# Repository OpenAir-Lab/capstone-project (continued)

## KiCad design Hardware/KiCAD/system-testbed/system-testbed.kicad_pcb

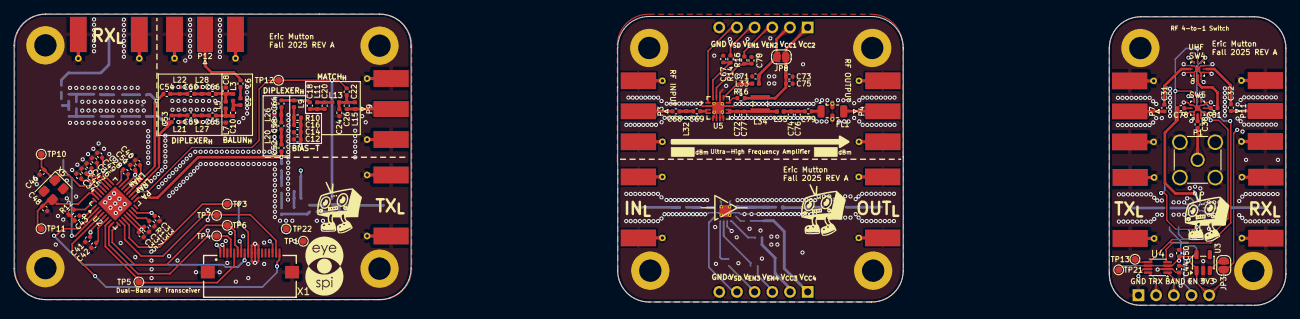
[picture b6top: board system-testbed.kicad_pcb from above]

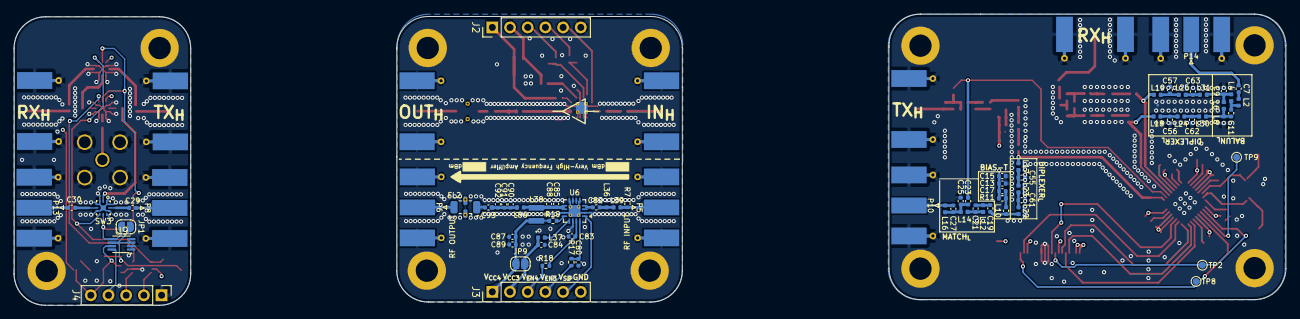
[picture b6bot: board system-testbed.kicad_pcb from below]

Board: 4 copper layers, 182.6 x 41.8 mm, 196 parts (76 on the bottom side), 110 nets.

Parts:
C6, C8, C10: 5.1pF; C_0402_1005Metric
C7, C9, C11, C21, C23: 12pF; C_0402_1005Metric
C12: 100p; C_0402_1005Metric
C13, C17, C38, C79, C88: 100pF; C_0402_1005Metric
C14, C40: 10n; C_0402_1005Metric
C15: 10nF; C_0402_1005Metric
C16: 56p; C_0402_1005Metric
C18: 39p; C_0402_1005Metric
C19: 82pF; C_0402_1005Metric
C20: 2.2p; C_0402_1005Metric
C22, C29, C30, C31, C32, C67, C70, C75, C78, C80, C81, C83, C89: 1nF; C_0402_1005Metric
C24: 6.2p; C_0402_1005Metric
C25: 15pF; C_0402_1005Metric
C26, C27: 1.2p; C_0402_1005Metric
C28: 1.5n; C_0402_1005Metric
C33, C34, C35, C36, C37, C41, C43, C45, C47, C49, C51: 47n; C_0402_1005Metric
C42: 220n; C_0402_1005Metric
C44, C50, C84: 1uF; C_0402_1005Metric
C46, C48: 15p; C_0402_1005Metric
C52, C53, C54, C64, C65, C66: 4.7pF; C_0402_1005Metric
C55, C56, C57, C61, C62, C63, C92: 18pF; C_0402_1005Metric
C58, C59, C60: 2.7pF; C_0402_1005Metric
C68: 10pF; C_0402_1005Metric
C69, C72: 33pF; C_0402_1005Metric
C71: 0.1uF; C_0402_1005Metric
C73, C87: 10uF; C_0402_1005Metric
C74: 27pF; C_0402_1005Metric
C76: 3pF; C_0402_1005Metric
C77: 6.8pF; C_0402_1005Metric
C82, C93: 220pF; C_0402_1005Metric
C85: 270pF; C_0402_1005Metric
C90, C91: 47pF; C_0402_1005Metric
FL1: LFCN-490; Filter_Mini-Circuits_FV1206
FL2: LFCN-160; Filter_Mini-Circuits_FV1206
H1, H1#2, H2, H3, H3#2, H4, H5, H5#2, H6, H8: M3; MountingHole_3.2mm_M3_ISO14580_Pad
J2, J3: Conn_01x06_Pin; PinHeader_1x06_P2.54mm_Vertical
J4: RF Switch; PinHeader_1x05_P2.54mm_Vertical
JP1, JP3: EN; SolderJumper-2_P1.3mm_Open_RoundedPad1.0x1.5mm
JP8, JP9: Single V_{CC}; SolderJumper-2_P1.3mm_Open_RoundedPad1.0x1.5mm
L1, L20, L21, L22, L26, L27, L28: 15nH; L_0402_1005Metric
L2: 39nH; L_0402_1005Metric
L3, L7: 27nH; L_0402_1005Metric
L4, L8: 82nH; L_0402_1005Metric
L5, L9: 56n; L_0402_1005Metric
L6: 150n; L_0402_1005Metric
L10: 220nH; C_0402_1005Metric
L11: 15n; L_0402_1005Metric
L12: 18nH; L_0402_1005Metric
L13: 43n; L_0402_1005Metric
L14, L23, L24, L25: 100nH; L_0402_1005Metric
L15: 22n; L_0402_1005Metric
L16, L17, L18, L19, L29, L30, L31, L39: 68nH; L_0402_1005Metric
L32: 10nH; L_0402_1005Metric
L33: 20nH; L_0402_1005Metric
L34: 23nH; 0908SQ23NGLC
L35: 2.4nH; L_0402_1005Metric
L36: 150nH; L_0402_1005Metric
L37: 56nH; L_0402_1005Metric
L38: 1uH; IND_IMSC1008AZER_VIS
L86: 9.1nH; L_0402_1005Metric
P1: SMA; SMA_Amphenol_901-144_Vertical
P3, P4, P5, P6, P7, P8, P9, P10, P11, P12, P13, P14: SMA; SMA_Molex_73251-1153_EdgeMount_Horizontal
R7: 350; R_0402_1005Metric
R10: 18; R_0402_1005Metric
R11: 22; R_0402_1005Metric
R12: 0R; R_0402_1005Metric
R13: 56k; R_0402_1005Metric
R14, R17: 1.27k; R_0402_1005Metric
R15, R18: 3.0k; R_0402_1005Metric
R16, R19: 0k; R_0402_1005Metric
SW3, SW4, SW5: SKY13330-397LF
TP1: +3.3V; TestPoint_Pad_D1.0mm
TP2: NRST; TestPoint_Pad_D1.0mm
TP3: NCS; TestPoint_Pad_D1.0mm
TP4: SCLK; TestPoint_Pad_D1.0mm
TP5: MOSI; TestPoint_Pad_D1.0mm
TP6: IO1/MISO; TestPoint_Pad_D1.0mm
TP7: IO0; TestPoint_Pad_D1.0mm
TP8: IO2; TestPoint_Pad_D1.0mm
TP9: IO3; TestPoint_Pad_D1.0mm
TP10: X1; TestPoint_Pad_D1.0mm
TP11: X2; TestPoint_Pad_D1.0mm
TP12: TRX_SW; TestPoint_Pad_D1.0mm
TP13: TRX_SW_{+2.5V}; TestPoint_Pad_D1.0mm
TP21: +2.5V; TestPoint_Pad_D1.0mm
TP22: GND; TestPoint_Pad_D1.0mm
U2: CC1200RHBR; QFN-32-1EP_5x5mm_P0.5mm_EP3.45x3.45mm
U3: LP5907MFX-2.5; SOT-23-5
U4, U9: TXS0101DBV; VSSOP-8_2.3x2mm_P0.5mm
U5, U6: GRF5604; QFN-16-1EP_3x3mm_P0.5mm_EP1.7x1.7mm_ThermalVias
U$22: EYESPI_MINI_LOGO
X1: EYESPI; Adafruit EYESPI FPC Connector
X5: 40 MHz; Crystal_SMD_3225-4Pin_3.2x2.5mm

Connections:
+2.5V: C50.2, JP1.1 (A), TP21.1, U3.5 (OUT), U4.3 (VCCA), U4.6 (OE), U9.3 (VCCA), U9.6 (OE)
+3.3V: C12.1, C13.1, C14.1, C15.1, C16.1, C17.1, C33.1, C35.1, C37.1, C41.1, C43.1, C44.2, C45.1, C47.1, C49.1, C51.1, C71.1, C84.1, J2.2, J3.2, J4.5, JP3.1 (A), JP8.1 (A), JP9.1 (A), L33.1, L37.1, R10.1, R11.1, SW3.9 (VDD), SW4.9 (VDD), SW5.9 (VDD), TP1.1, U2.1 (VDD_GUARD), U2.5 (DVDD), U2.12 (DVDD), U2.13 (AVDD_IF), U2.15 (AVDD_RF), U2.22 (AVDD_SYNTH1), U2.25 (AVDD_PFD_CHP), U2.27 (AVDD_SYNTH2), U2.28 (AVDD_XOSC), U3.1 (IN), U4.7 (VCCB), U9.7 (VCCB), X1.1, X1.2, X1.7, X1.16
/RF Subsystem/EN_{BAND}: JP1.2 (B), SW3.8 (EN), SW4.8 (EN), SW5.8 (EN), U9.5 (A1)
/RF Subsystem/LNA_N: C54.1, L19.1, U2.20 (LNA_N)
/RF Subsystem/LNA_N_{UHF}: C8.1, C66.2, L3.1, L5.2
/RF Subsystem/LNA_N_{VHF}: C9.1, L4.1, L6.2, L31.2
/RF Subsystem/LNA_P: C53.1, L18.1, U2.19 (LNA_P)
/RF Subsystem/LNA_P_{UHF}: C10.1, C65.2, L5.1, L7.1
/RF Subsystem/LNA_P_{VHF}: C11.1, L6.1, L8.1, L30.1
/RF Subsystem/PA_{SHUTDOWN}: TP9.1, U2.3 (GPIO3)
/RF Subsystem/PA_{UHF}: C18.2, C64.2, L9.2
/RF Subsystem/PA_{VHF}: C19.2, L10.2, L29.2
/RF Subsystem/RF Frontend/RX_{UHF}: C32.1, P11.1 (In)
/RF Subsystem/RF Frontend/RX_{VHF}: C30.1, P13.1 (In)
/RF Subsystem/RF Frontend/TX_{UHF}: C31.1, P7.1 (In)
/RF Subsystem/RF Frontend/TX_{VHF}: C29.1, P8.1 (In)
/RF Subsystem/RF Frontend/UHF 6W PA/RF_{IN}: C68.1, P3.1 (In)
/RF Subsystem/RF Frontend/UHF 6W PA/RF_{OUT}: C79.2, FL1.1 (IN)
/RF Subsystem/RF Frontend/UHF 6W PA/V_{CC2}: C73.1, C75.1, J2.1, JP8.2 (B), L34.1, R16.2
/RF Subsystem/RF Frontend/UHF 6W PA/V_{EN1}: C67.1, R14.1, U5.16 (V_{ENABLE1})
/RF Subsystem/RF Frontend/UHF 6W PA/V_{EN2}: C70.1, R15.1, U5.15 (V_{ENABLE2})
/RF Subsystem/RF Frontend/UHF 6W PA/V_{ENABLE1}: J2.4, R14.2
/RF Subsystem/RF Frontend/UHF 6W PA/V_{ENABLE2}: J2.3, R15.2
/RF Subsystem/RF Frontend/UHF 6W PA/V_{SHUTDOWN}: J2.5, U5.1 (V_{SHUTDOWN})
/RF Subsystem/RF Frontend/VHF 6W PA/RF_{IN}: L39.1, P5.1 (In), R7.2
/RF Subsystem/RF Frontend/VHF 6W PA/RF_{OUT}: C93.2, FL2.1 (IN)
/RF Subsystem/RF Frontend/VHF 6W PA/V_{CC2}: C87.1, C89.1, J3.1, JP9.2 (B), L38.1, R19.2
/RF Subsystem/RF Frontend/VHF 6W PA/V_{EN1}: C80.1, R17.1, U6.16 (V_{ENABLE1})
/RF Subsystem/RF Frontend/VHF 6W PA/V_{EN2}: C83.1, R18.1, U6.15 (V_{ENABLE2})
/RF Subsystem/RF Frontend/VHF 6W PA/V_{ENABLE1}: J3.4, R17.2
/RF Subsystem/RF Frontend/VHF 6W PA/V_{ENABLE2}: J3.3, R18.2
/RF Subsystem/RF Frontend/VHF 6W PA/V_{SHUTDOWN}: J3.5, U6.1 (V_{SHUTDOWN})
/RF Subsystem/RFSW_{BAND}: J4.3, U4.1 (B2)
/RF Subsystem/RFSW_{EN}: J4.4, U9.8 (B1)
/RF Subsystem/RFSW_{TRX}: J4.2, U4.8 (B1)
/RF Subsystem/SW_BAND: SW5.7 (CTRL), U4.4 (A2)
/RF Subsystem/SW_TRX: SW3.7 (CTRL), SW4.7 (CTRL), TP13.1, U4.5 (A1)
/RF Subsystem/TRX_GPIO0: TP7.1, U2.10 (GPIO0), X1.17
/RF Subsystem/TRX_GPIO2: TP8.1, U2.4 (GPIO2), X1.18
/RF Subsystem/TRX_MISO: TP6.1, U2.9 (SO(GPIO1)), X1.6
/RF Subsystem/TRX_MOSI: TP5.1, U2.7 (SI), X1.5
/RF Subsystem/TRX_NCS: TP3.1, U2.11 (~CS), X1.9
/RF Subsystem/TRX_NRST: TP2.1, U2.2 (~RESET), X1.8
/RF Subsystem/TRX_PA: C52.1, L17.1, U2.17 (PA)
/RF Subsystem/TRX_SCLK: TP4.1, U2.8 (SCLK), X1.4
/RF Subsystem/TRX_X1: C46.2, TP10.1, U2.30 (XOSC_Q1), X5.1
/RF Subsystem/TRX_X2: C48.1, TP11.1, U2.31 (XOSC_Q2), X5.3
/RF Subsystem/TRX_{SW}: C22.1, C23.1, TP12.1, U2.18 (TRX_SW)
GND: C8.2, C9.2, C12.2, C13.2, C14.2, C15.2, C24.2, C25.2, C33.2, C34.2, C35.2, C36.2, C37.2, C40.2, C41.2, C42.2, C43.2, C44.1, C45.2, C46.1, C47.2, C48.2, C49.2, C50.1, C51.2, C55.2, C56.2, C57.2, C61.2, C62.2, C63.2, C67.2, C70.2, C71.2, C72.2, C73.2, C74.2, C75.2, C76.2, C77.2, C80.2, C83.2, C84.2, C85.2, C87.2, C88.2, C89.2, C90.2, C91.2, C92.2, FL1.2 (GND), FL1.4 (GND), FL2.2 (GND), FL2.4 (GND), H1.1, H1#2.1, H2.1, H3.1, H3#2.1, H4.1, H5.1, H5#2.1, H6.1, H8.1, J2.6, J3.6, J4.1, L7.2, L8.2, L20.2, L21.2, L22.2, L26.2, L27.2, L28.2, L32.2, L36.2, P1.2 (Ext), P3.2 (Ext), P4.2 (Ext), P5.2 (Ext), P6.2 (Ext), P7.2 (Ext), P8.2 (Ext), P9.2 (Ext), P10.2 (Ext), P11.2 (Ext), P12.2 (Ext), P13.2 (Ext), P14.2 (Ext), R7.1, R12.1, R13.2, SW3.1 (GND), SW3.3 (GND), SW3.4 (GND), SW3.6 (GND), SW3.10 (GND), SW3.12 (GND), SW3.13 (GND), SW4.1 (GND), SW4.3 (GND), SW4.4 (GND), SW4.6 (GND), SW4.10 (GND), SW4.12 (GND), SW4.13 (GND), SW5.1 (GND), SW5.3 (GND), SW5.4 (GND), SW5.6 (GND), SW5.10 (GND), SW5.12 (GND), SW5.13 (GND), TP22.1, U2.33 (GND_EP), U3.2 (GND), U4.2 (GND), U5.2 (GND/NC), U5.5 (GND/NC), U5.6 (GND/NC), U5.7 (GND/NC), U5.8 (GND/NC), U5.11 (GND/NC), U5.14 (GND/NC), U5.17 (PAD), U6.2 (GND/NC), U6.5 (GND/NC), U6.6 (GND/NC), U6.7 (GND/NC), U6.8 (GND/NC), U6.11 (GND/NC), U6.14 (GND/NC), U6.17 (PAD), U9.2 (GND), X1.3, X1.10, X1.11, X1.12, X1.Z1, X1.Z2, X5.2, X5.4
unnamed: C6.2, L1.1
unnamed: C7.2, L2.1
unnamed: C10.2, L1.2, L3.2
unnamed: C11.2, L2.2, L4.2
unnamed: C16.2, L9.1, R10.2
unnamed: C17.2, L10.1, R11.2
unnamed: C18.1, C20.2, L11.1
unnamed: C19.1, C21.2, L12.1
unnamed: C20.1, L11.2, L13.1
unnamed: C21.1, L12.2, L14.1
unnamed: C22.2, C24.1, C26.1, L13.2, L15.1
unnamed: C23.2, C25.1, C27.1, L14.2, L16.1
unnamed: C52.2, C58.1, L20.1
unnamed: C53.2, C59.1, L21.1
unnamed: C54.2, C60.1, L22.1
unnamed: C55.1, L17.2, L23.1
unnamed: C56.1, L18.2, L24.1
unnamed: C57.1, L19.2, L25.1
unnamed: C58.2, C64.1, L26.1
unnamed: C59.2, C65.1, L27.1
unnamed: C60.2, C66.1, L28.1
unnamed: C61.1, L23.2, L29.1
unnamed: C62.1, L24.2, L30.2
unnamed: C63.1, L25.2, L31.1
unnamed: C68.2, C69.1, L32.1
unnamed: C69.2, U5.3 (RF_{IN}), U5.4 (RF_{IN})
unnamed: C72.1, C77.1, L34.2, L35.1, U5.9 (RF_{OUT}), U5.10 (RF_{OUT})
unnamed: C74.1, C76.1, C79.1, L35.2
unnamed: C82.1, L36.1, L39.2
unnamed: C82.2, U6.3 (RF_{IN}), U6.4 (RF_{IN})
unnamed: C85.1, C88.1, L38.2, L86.1, U6.9 (RF_{OUT}), U6.10 (RF_{OUT})
unnamed: C90.1, C91.1, C92.1, C93.1, L86.2
unnamed: FL1.3 (OUT), P4.1 (In)
unnamed: FL2.3 (OUT), P6.1 (In)
unnamed: JP3.2 (B), U3.3 (EN)
unnamed: C38.1, P1.1 (In)
unnamed: C26.2, L15.2, P9.1 (In)
unnamed: C27.2, L16.2, P10.1 (In)
unnamed: C6.1, P12.1 (In)
unnamed: C7.1, P14.1 (In)
unnamed: C78.1, SW3.2 (RF1_COM)
unnamed: C29.2, SW3.11 (RF2)
unnamed: C30.2, SW3.5 (RF3)
unnamed: C81.1, SW4.2 (RF1_COM)
unnamed: C31.2, SW4.11 (RF2)
unnamed: C32.2, SW4.5 (RF3)
unnamed: C38.2, SW5.2 (RF1_COM)
unnamed: C78.2, SW5.11 (RF2)
unnamed: C81.2, SW5.5 (RF3)
unnamed: C42.1, U2.6 (DCPL)
unnamed: C36.1, U2.26 (DCPL_PFD_CHP)
unnamed: C40.1, U2.21 (DCPL_VCO)
unnamed: C34.1, U2.29 (DCPL_XOSC)
unnamed: R12.2, U2.32 (EXT_XOSC)
unnamed: C28.2, U2.23 (LPF0)
unnamed: C28.1, U2.24 (LPF1)
unnamed: R13.1, U2.14 (RBIAS)
unnamed: R16.1, U5.12 (V_{BIAS})
unnamed: L33.2, U5.13 (V_{CC1})
unnamed: R19.1, U6.12 (V_{BIAS})
unnamed: L37.2, U6.13 (V_{CC1})

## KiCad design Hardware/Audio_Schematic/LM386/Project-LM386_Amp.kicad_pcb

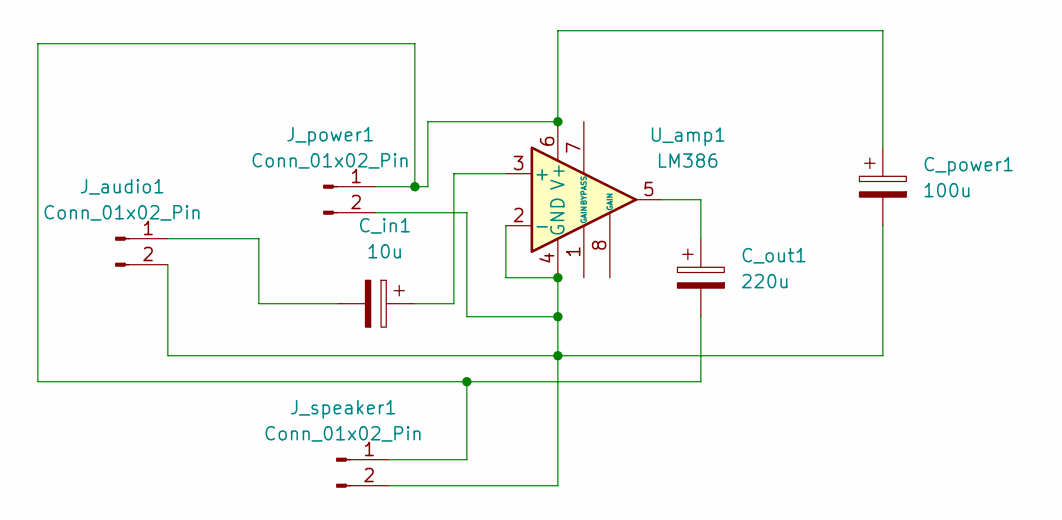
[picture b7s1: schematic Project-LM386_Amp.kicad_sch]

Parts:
C_in1: 10u; CP_Elec_6.3x5.3
C_out1: 220u; CP_Elec_6.3x5.3
C_power1: 100u; CP_Elec_6.3x5.3
J_audio1: Conn_01x02_Pin; PinHeader_1x02_P2.54mm_Vertical
J_power1: Conn_01x02_Pin; PinHeader_1x02_P2.54mm_Vertical
J_speaker1: Conn_01x02_Pin; PinHeader_1x02_P2.54mm_Vertical
U_amp1: LM386; HSOP-8-1EP_3.9x4.9mm_P1.27mm_EP2.3x2.3mm

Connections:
unnamed: C_out1.1, U_amp1.5
unnamed: C_in1.2, J_audio1.1
unnamed: C_power1.2, J_audio1.2, J_power1.2, J_speaker1.2, U_amp1.2 (-), U_amp1.4 (GND)
unnamed: C_out1.2, C_power1.1, J_power1.1, J_speaker1.1, U_amp1.6 (V+)
unnamed: C_in1.1, U_amp1.3 (+)

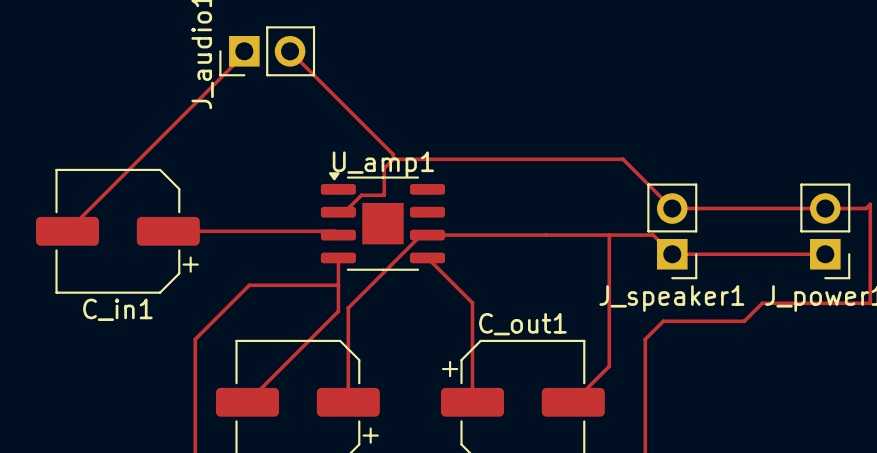
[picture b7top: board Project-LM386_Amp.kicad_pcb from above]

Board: 2 copper layers, 7 parts (0 on the bottom side), 5 nets.

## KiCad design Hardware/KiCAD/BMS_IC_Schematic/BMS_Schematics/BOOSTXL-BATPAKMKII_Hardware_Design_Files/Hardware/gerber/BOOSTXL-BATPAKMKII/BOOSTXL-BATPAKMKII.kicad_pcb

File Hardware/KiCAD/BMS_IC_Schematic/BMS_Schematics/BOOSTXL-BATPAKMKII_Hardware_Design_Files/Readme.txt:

BOOSTXL-BATPAKMKII Hardware Design Files v1.00.00
Texas Instruments, Inc.

********************************************************************************
Welcome to the BOOSTXL-BATPAKMKII BoosterPack!
********************************************************************************

In this package, you will find hardware design files that can help you quickly
get started on developing your own project.

Available in the 'Hardware' folder are the complete board schematic and layout,
bill of material, and Gerber files.

You can also find various web links in the 'Documentation' folder pointing to
the Tool Page, Quick Start Guide, and User's Guide.

For more resources, be sure to visit www.ti.com/tool/boostxl-batpakmkii

********************************************************************************
Revision History
********************************************************************************
Ver 1.00.00 - June 3rd, 2016
- Initial Release

********************************************************************************
Project File Listing
********************************************************************************
|--Documentation                      : Folder containing links to more resources
|--Hardware                           : Folder containing hardware design files,
                                        bill of material and gerber files
|--Readme.txt                         : This file

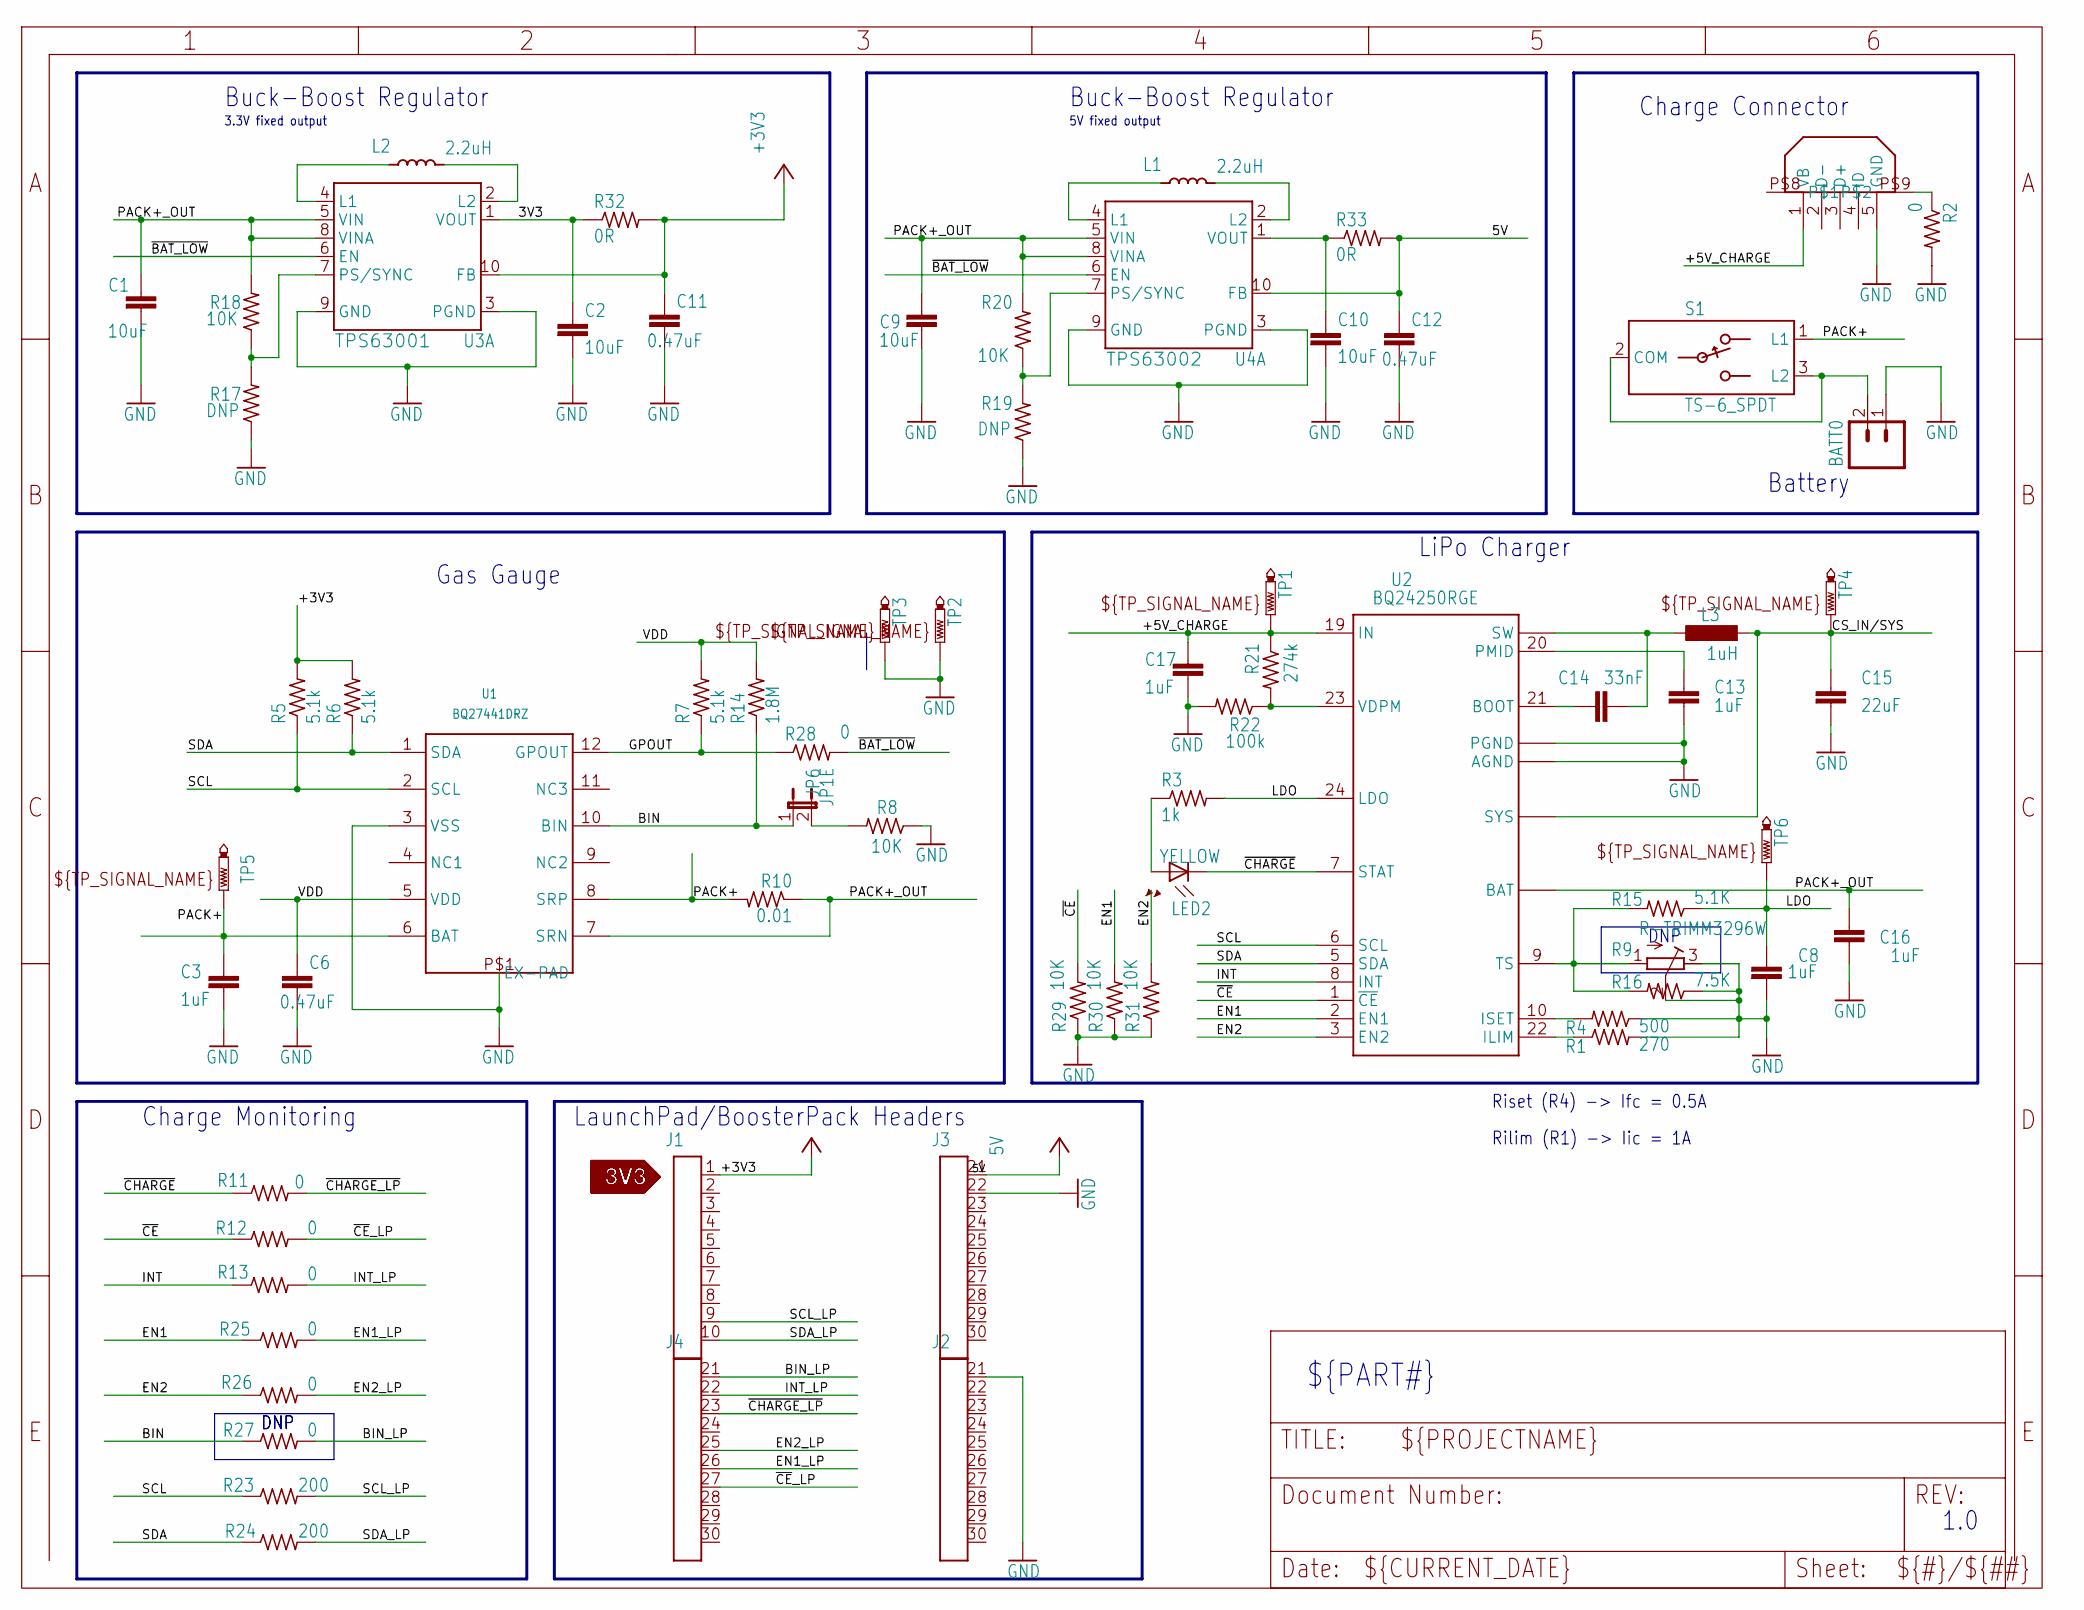
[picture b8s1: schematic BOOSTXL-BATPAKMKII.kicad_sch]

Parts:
BATT0: M02-JST-2MM-SMT; JST-2-SMD
C1, C2, C9, C10: 10uF; C0603
C3, C8, C13, C16, C17: 1uF; C0603
C6, C11, C12: 0.47uF; C0603
C14: 33nF; C0603
C15: 22uF; C0603
J1: HEADER1X10; 1X10
J2, J3, J4: HEADER1X10-J3; 1X10-J3
JP6: JP1E; JP1
L1, L2: 2.2uH; VLF4102A
L3: 1uH; L3216C
LED2: YELLOW; RIGHTANGLE_1208
R1: 270; R0603
R2, R11, R12, R13, R25, R26, R27, R28: 0; R0603
R3: 1k; R0603
R4: 500; R0603
R5, R6, R7: 5.1k; R0603
R8, R18, R20, R29, R30, R31: 10K; R0603
R9: R-TRIMM3296W; RTRIM3296W
R10: 0.01; R1206
R14: 1.8M; R0603
R15: 5.1K; R0603
R16: 7.5K; R0603
R17, R19: DNP; R0603
R21: 274k; R0603
R22: 100k; R0603
R23, R24: 200; R0603
R32, R33: 0R; R0805
S1: TS-6_SPDT
TP1, TP2, TP3, TP4, TP5, TP6: PTR1PAD1-13; P1-13
U1: BQ27441DRZ; DRZ12
U2: BQ24250RGE; TI_RGE24
U3: TPS63001; DRC-S-PVSON-N10
U4: TPS63002; DRC-S-PVSON-N10
U$1: SILK_3V3_TAG
U$2: MS_(TM)
USB0: CONN_USB_MICRO_B; USB_MICRO_B_SMT

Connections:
3V3: C2.1, R32.1, U3.1 (VOUT)
5V: C12.1, J3.21 (1), R33.2, U4.10 (FB)
+3V3: C11.1, J1.1, R5.2, R6.2, R32.2, U3.10 (FB)
+5V_CHARGE: C17.1, R21.1, TP1.TP, U2.19 (IN), USB0.1 (VB)
BIN: JP6.1, R14.1, R27.1, U1.10 (BIN)
BIN_LP: J4.21 (1), R27.2
CS_IN/SYS: C15.1, L3.2, TP4.TP, U2.13 (SYS), U2.14 (SYS)
EN1: R25.1, R30.2, U2.2 (EN1)
EN1_LP: J4.26 (6), R25.2
EN2: R26.1, R31.2, U2.3 (EN2)
EN2_LP: J4.25 (5), R26.2
GND: BATT0.1, C1.2, C2.2, C3.2, C6.2, C8.2, C9.2, C10.2, C11.2, C12.2, C13.2, C15.2, C16.2, C17.2, J2.21 (1), J3.22 (2), R1.2, R2.2, R4.1, R8.1, R9.2 (S), R9.3 (A), R16.1, R17.1, R19.1, R22.2, R29.1, R30.1, R31.1, TP2.TP, TP3.TP, U1.3 (VSS), U1.P$1 (EX-PAD), U2.4 (AGND), U2.15 (PGND), U2.16 (PGND), U2.P$1 (AGND), U3.3 (PGND), U3.9 (GND), U4.3 (PGND), U4.9 (GND), USB0.5 (GND)
GPOUT: R7.1, R28.1, U1.12 (GPOUT)
INT: R13.1, U2.8 (INT)
INT_LP: J4.22 (2), R13.2
LDO: C8.1, R3.2, R15.1, TP6.TP, U2.24 (LDO)
unnamed: L2.P$3, U3.4 (L1)
unnamed: L2.P$1, U3.2 (L2)
unnamed: L1.P$3, U4.4 (L1)
unnamed: JP6.2, R8.2
unnamed: LED2.ANODE (A), R3.1
unnamed: L1.P$1, U4.2 (L2)
unnamed: R9.1 (E), R15.2, R16.2, U2.9 (TS)
unnamed: R21.2, R22.1, U2.23 (VDPM)
unnamed: C13.1, U2.20 (PMID)
unnamed: C14.1, U2.21 (BOOT)
unnamed: C14.2, L3.1, U2.17 (SW), U2.18 (SW)
unnamed: BATT0.2, S1.2 (COM), S1.3 (L2)
unnamed: R4.2, U2.10 (ISET)
unnamed: R2.1, USB0.P$9
unnamed: R17.2, R18.1, U3.7 (PS/SYNC)
unnamed: R19.2, R20.1, U4.7 (PS/SYNC)
unnamed: R1.1, U2.22 (ILIM)
unnamed: C10.1, R33.1, U4.1 (VOUT)
PACK+: C3.1, R10.2, S1.1 (L1), TP5.TP, U1.6 (BAT), U1.8 (SRP)
PACK+_OUT: C1.1, C9.1, C16.1, R10.1, R18.2, R20.2, U1.7 (SRN), U2.11 (BAT), U2.12 (BAT), U3.5 (VIN), U3.8 (VINA), U4.5 (VIN), U4.8 (VINA)
SCL: R5.1, R23.1, U1.2 (SCL), U2.6 (SCL)
SCL_LP: J1.9, R23.2
SDA: R6.1, R24.1, U1.1 (SDA), U2.5 (SDA)
SDA_LP: J1.10, R24.2
VDD: C6.1, R7.2, R14.2, U1.5 (VDD)
~BAT_LOW: R28.2, U3.6 (EN), U4.6 (EN)
~CE: R12.1, R29.2, U2.1 (~CE)
~CE_LP: J4.27 (7), R12.2
~CHARGE_LP: J4.23 (3), R11.2
~CHARGE: LED2.CATHODE (C), R11.1, U2.7 (STAT)

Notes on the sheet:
3.3V fixed output
${COMPANY}
1.0
Charge Connector
Charge Monitoring
5V fixed output
Buck-Boost Regulator
Riset (R4) -> Ifc = 0.5A
DNP
LiPo Charger
${PART#}
Rilim (R1) -> Iic = 1A
Gas Gauge
LaunchPad/BoosterPack Headers
Battery

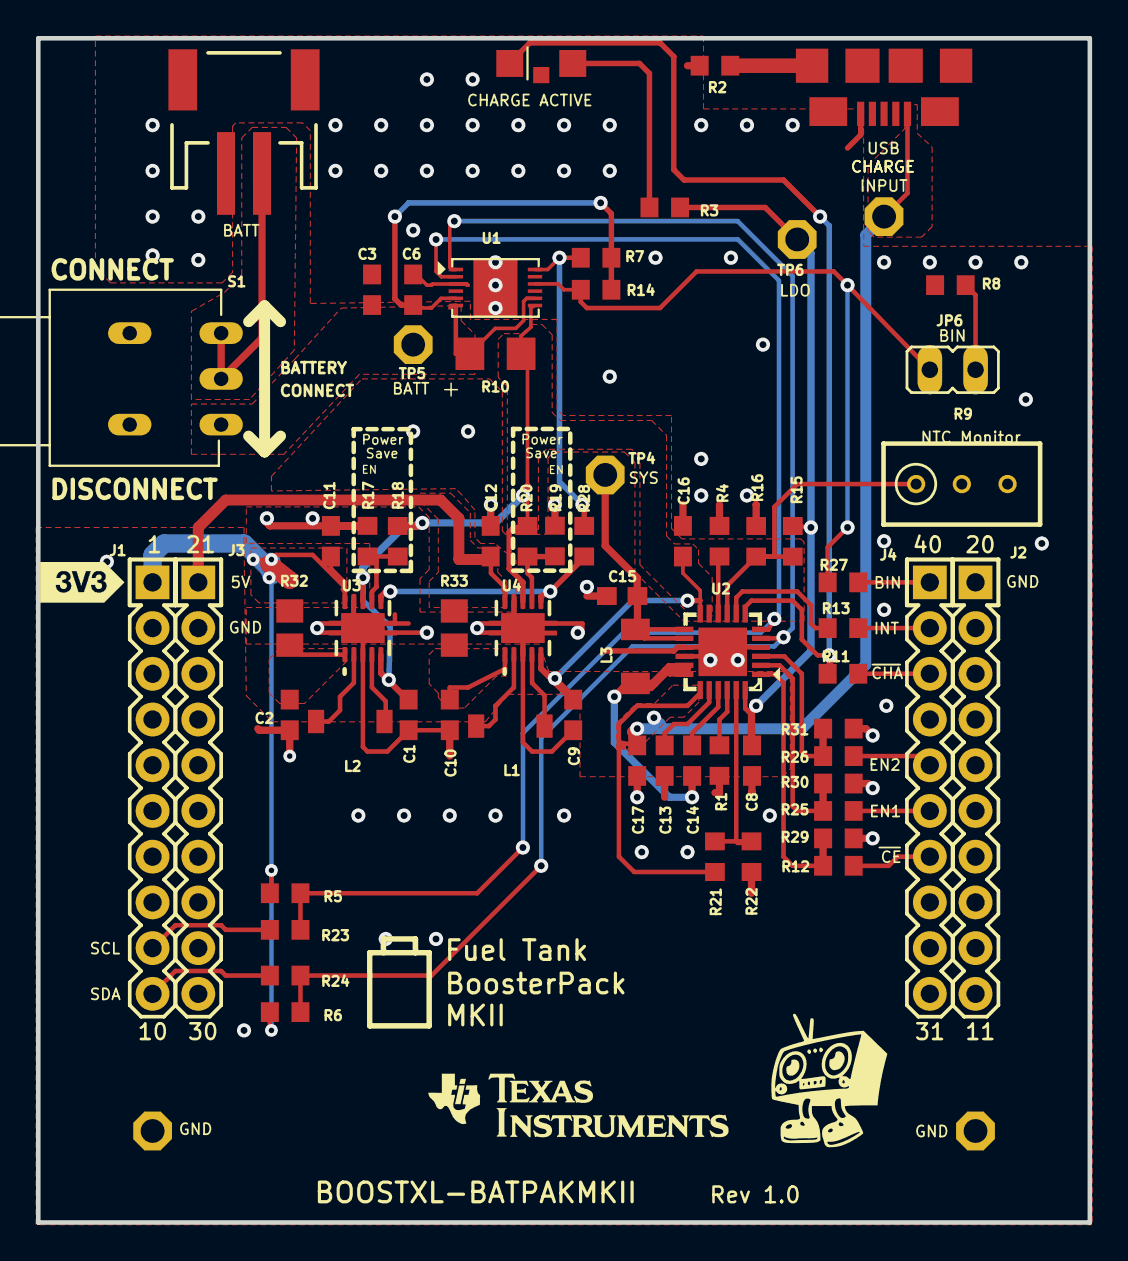
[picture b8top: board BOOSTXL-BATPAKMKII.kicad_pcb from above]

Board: 2 copper layers, 58.4 x 65.8 mm, 73 parts (0 on the bottom side), 46 nets.

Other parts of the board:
DRAW3: LOGO-ROCKET-10X7MM-BRD
U$4: LOGO16_TPLACE

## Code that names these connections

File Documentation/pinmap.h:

#pragma once
#include <Arduino.h>

/*  
 * ---------------------------------------------------------
 *  OpenAir Lab — ESP32-WROVER-E Pin Map
 *  Structured namespace layout for subsystem drivers.
 *  
 *  SOURCE: OpenAir Lab – Pin Map (MCU vs Expander) – V1
 * ---------------------------------------------------------
 */

namespace pins {

    /* =====================
     *  SPI — CC1200 Radio
     * ===================== */
    namespace cc1200 {
        constexpr uint8_t SCK   = 18;   // VSPI_SCK — high-speed
        constexpr uint8_t MOSI  = 23;   // VSPI_MOSI
        constexpr uint8_t MISO  = 19;   // VSPI_MISO
        constexpr uint8_t CS    = 5;    // VSPI_CS — STRAP pin, pulled up externally
        constexpr uint8_t GDO0  = 32;   // interrupt (latency-critical)
        constexpr uint8_t GDO2  = 33;   // interrupt (latency-critical)
        // RESET moved to expander (slow-rate control)
    }


    /* =====================
     *  SPI — TFT ST7789 via EYESPI
     * ===================== */
    namespace tft {
        constexpr uint8_t SCK   = 14;   // HSPI_SCK
        constexpr uint8_t MOSI  = 13;   // HSPI_MOSI
        constexpr uint8_t CS    = 15;   // TFT_CS — pull-up required at boot
        constexpr uint8_t DC    = 4;    // Data/Command
        // RST, BL_EN handled by expander
        // TE (optional): GPIO36 if VSYNC needed
        constexpr uint8_t TE    = 36;   // optional tearing-effect input (unused = ignore)
    }


    /* =====================
     *  I²S — Audio System (ICS-43434 mic + MAX98357A amp)
     * ===================== */
    namespace audio {
        constexpr uint8_t BCLK  = 26;   // I²S bit clock
        constexpr uint8_t LRCLK = 25;   // I²S left/right clock
        constexpr uint8_t DOUT  = 27;   // ESP32 → MAX98357A
        constexpr uint8_t DIN   = 34;   // ICS-43434 mic → ESP (input-only GPIO)
        // AMP_SD, GAIN via I²C expander
    }


    /* =====================
     *  I²C — Shared Control Bus (PD, Fuel Gauge, GPIO Expander)
     * ===================== */
    namespace i2c {
        constexpr uint8_t SDA   = 21;
        constexpr uint8_t SCL   = 22;
    }


    /* =====================
     *  GPIO Expander Interrupt → MCU
     * ===================== */
    namespace expander {
        constexpr uint8_t INT   = 35;   // expander → MCU, GPIO35 input-only
    }


    /* =====================
     *  Power & System Functions
     * ===================== */
    namespace system_pins {
        // Boot/strap pins intentionally avoided except where needed
        // GPIO0, GPIO2, GPIO12 — DO NOT use for peripherals
        // GPIO5, GPIO15 — safe after boot if pulled up

        constexpr uint8_t BOOT_BUTTON  = 0;   // physical BOOT, if wired
        constexpr uint8_t EN_PIN       = -1;  // EN is not a GPIO; controlled via CH340/esp-prog circuitry
    }


    /* =====================
     *  Optional MCU-side Inputs
     * ===================== */
    namespace optional {
        constexpr uint8_t ROT_A = 16;  // if rotary encoder moved to MCU
        constexpr uint8_t ROT_B = 17;
    }

} // namespace pins

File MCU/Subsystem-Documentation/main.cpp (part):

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// cc1200.pin_sck, cc1200.pin_miso, cc1200.pin_mosi, cc1200.pin_ss
cc1200_config_t cc1200;
#define RFSW_ENABLE  8
#define RFSW_BAND    9
#define RFSW_TRX     10
sky13330_config_t sky13330;
#define UHF_ENABLE1  15
#define UHF_ENABLE2  14 // bands share enables
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#define TFT_DC   26 // Display Command pin
#define TFT_MOSI 13 // ESP32 IOMUX Default
#define TFT_SCLK 14 // ESP32 IOMUX Default
#define TFT_RST  -1 // Not connected
st7789_config_t display_config;

Adafruit_ST7789 tft = Adafruit_ST7789(TFT_SS, TFT_DC, TFT_MOSI, TFT_SCLK, TFT_RST);
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    display_config.pin_dc = TFT_DC;
    display_config.pin_mosi = TFT_MOSI;
    display_config.pin_sclk = TFT_SCLK;
    display_config.pin_reset = TFT_RST;

    while (!(pcf8575_init(pcf_hmi, pcf_hmi_config) == 0));
    while (!(display_init(display_config) == 0));
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    // attachInterrupt(digitalPinToInterrupt(pcf_mcu_config.pin_interrupt), inputISR, CHANGE);
    // Skyworks SKY13330-397LF SPDT RF Switch
    sky13330.pin_enable = RFSW_ENABLE;
    sky13330.pin_band = RFSW_BAND;
    sky13330.pin_trx = RFSW_TRX;
    // GuerrillaRF GRF5604 RF Amplifier
    uhf_grf5604.band = UHF;
    uhf_grf5604.pin_shutdown = UHF_SHUTDOWN;
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    while(!Wire.begin());

    // ESP32 I2S0 Interface
    max98357a.pin_bclk = I2S0_PIN_BCLK;
    max98357a.pin_lrclk = I2S0_PIN_LRCLK;
    max98357a.pin_data_in = I2S0_PIN_DOUT;
    ics43434.pin_bclk = I2S0_PIN_BCLK;
    ics43434.pin_lrclk = I2S0_PIN_LRCLK;
    ics43434.pin_data_out = I2S0_PIN_DIN;
    ics43434.sample_rate = I2S0_SAMPLE_RATE;
    ics43434.bits_per_sample = I2S0_WORD_SIZE;
    #ifdef DEBUG
    DEBUG.printf("(I2S0 -----) Beginning use of I2S0 Interface... "
        "[BCLK=%d, LRCLK=%d, DOUT=%d, DIN=%d]\n", I2S0_PIN_BCLK, I2S0_PIN_LRCLK, max98357a.pin_data_in, ics43434.pin_data_out 
    );
    #endif
    I2S.begin(I2S_PHILIPS_MODE, I2S0_SAMPLE_RATE, I2S0_WORD_SIZE);
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
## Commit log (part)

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2025-07-18 Create WROVER-documentation.md
    File for documentation purposes
2025-07-18 Update WROVER-documentation.md
    content
2025-07-19 feat: begin recapture & document RF Power Amplifier
2025-07-19 feat: begin recapture & document RF Transceiver
2025-07-19 feat: recapture and documentation on BMS IC's
2025-07-21 docs: I2S Protocol #13
2025-07-22 feat: begin annotating eval module BoM #7
2025-07-22 feat: include past meeting notes
2025-07-22 Create PDR-July 21.md
    Meeting notes. Everyone please look at this and add to it !!
2025-07-26 Doc: Audio Amplifier Schematic
2025-08-18 feat: begin system testbed schematic capture
2025-08-19 chore: co-locate vendor evaluation recaptures #6
2025-08-19 feat: capture Switched Analog Volume Potentometer and Switched Quadrate Rotary Encoder #15
2025-08-19 feat: capture 4x4 Keypad Module #15
2025-08-19 feat: begin importing Battery Management System capture in new power subsystem sheet #3 #21
2025-08-19 feat: begin RF subsystem capture #7 #16
2025-08-20 feat: complete recapture of Adafruit Mic Module
2025-08-21 feat: begin dedicated sheets for RF switch throws, refine PA RFIC symbol #34
2025-08-22 feat: refine rf subsystem sheet, specify band selection from two tuned PAs #34
2025-08-25 chore: revise RF switch symbol description #34
2025-08-25 feat: complete RF switches, revise RF sheet structure #34
2025-08-25 feat: assign RF netclass to RF signal paths #34
2025-08-27 Create August 25 - First Meeting of Senior Design 2.md
    8.26 Meeting with the Team - please read
2025-08-29 feat: capture EYESPI display connectors #15
2025-08-29 feat: plot system testbed #41
2025-08-29 feat: re-sized PSU box KiCAD Runthrough Fixes #30
2025-09-02 docs: added a some brief notes taken in the workflow meetig (these will need to be expanded upon)
2025-09-03 feat: testing commit
2025-09-03 feat: import board stackup of OSHPark Prototype Service #57
2025-09-03 fix: create real EYESPI FPC connector symbol and footprint #57
2025-09-03 feat: assign 0603 passive component footprints #32 #34
2025-09-03 chore: ignore .DS_Store files
2025-09-03 not sure what changes were made for this but I'm committing for posterity
2025-09-04 docs: draft recapture of Modulino for Templating #57
2025-09-04 fix: move port expander over to HMI schematic #15 #33
2025-09-04 fix: relabel TRX GPIOs to breakout over EYESPI #34 #65
2025-09-04 docs: Pin Mapping Table for MCU and all interconnected subsystems
2025-09-04 Rename Pin Mapping Table to Pin Mapping Table.md
    markdown file
2025-09-05 feat: Testing Sync
2025-09-06 chore: set pad size defaults
2025-09-06 feat: create Hello World in ESP-IDF using PlatformIO
2025-09-06 datasheets and added esp32 symbol
2025-09-06 fix: added WROVER symbol to project library and schematic
2025-09-07 Update Pin Mapping Table.md
    need to find alternative for STUSB4500 GPIO
2025-09-08 audio-subsystem schematic update Audio PCB Fixes #32
2025-09-09 feat: update MCU schematic
2025-09-09 fix: add power devices to library
2025-09-09 fix: relocate sheets on testbench
2025-09-10 Feat(Library): Add batch of new power ICs
2025-09-11 feat: add RF switch with built-in decoder #65
2025-09-11 chore: pin project footprint library
2025-09-11 fix: remove mounting holes for unused HW-834 keypad #69
2025-09-11 fix: standardize size symbol pins of RF switch to 2.54mm #65
2025-09-11 feat: begin use of discrete diplexers over band select switches #65 feat: redraw rx/tx switching with built-in decode plus level shifting #34 feat: begin RF modulino testpoints #45
2025-09-11 chore: replot system testbed #41
2025-09-11 Update-Jumper-Schematic
2025-09-12 feat: capture Audio PCB #32 feat: begin I2S Pin Mapping and Interconnects #53
2025-09-12 fix: clarify labellng and pin head #32
2025-09-12 fix: rename #32
2025-09-12 fix: import RF sheet contents #65
2025-09-12 feat: move modulino interconnects to root sheet #57
2025-09-12 fix: correct input and output for labels #51
2025-09-12 fix: remove EYESPI from HMI sheet #69
2025-09-12 feat: pin relabel #63
2025-09-12 fix: reannotate and resolve power nets #51
2025-09-12 feat: schematic capture #63
2025-09-13 fix: Cleaned up structure of BMS PSU Schematic Capture Fixes #51
2025-09-13 Create Workflow Runthrough #2.md
    Summary of what was covered in Weekly Workflow 2
2025-09-13 Create Workflow Runthrough #4.md
    summary of workflow 4 - advanced PCB tools
2025-09-13 Create september 4 - Team Slide Review.md
    Slide review from the week we did not have an advisor meeting
2025-09-13 feat: added WROVER footprint to project library & symbol
2025-09-13 feat: added WROVER footprint to project library & symbol - MCU Schematic capture Fixes #63
2025-09-13 fix: fixing labels PSU Schematic Capture Fixes #51
2025-09-13 fix: reannotate schematics for pcb editor use #55
2025-09-14 Feat: Added ICs & Completed schematic for the other blocks
2025-09-14 Revert "Feat: Added ICs & Completed schematic for the other blocks"
    This reverts commit 5ccb9a6ab9d8f693594799fe98ca877545035d56.
2025-09-14 Fix: Changed IC positions
2025-09-14 Feat: Added footprint for TVS Diode
2025-09-18 fix: remove unused mounting holes for HW #69 fix: edit symbol fields of button matrix #69
2025-09-18 fix: recover audio schematic #70
2025-09-18 feat: swap to vertical rotary encoder used by Modulino Knob #69
2025-09-23 fix: allow for DRC use in PCB editor by successful reannotation
2025-09-24 feat: begin arduino framework instead of arduino component compatibility #12
2025-09-24 feat: include Adafruit ST7789 demo and begin #15
2025-09-24 feat: begin transceiver driver and capture command strobes #12
2025-10-02 feat: update pinouts for mcu #53
2025-10-12 Create Oct 9 Team Meeting.md
    Slide Review meeting (members only)
2025-10-16 Create Oct 14 Workshop - PlatformIO.md
    PlatformIO and next steps
2025-10-22 chore: remove .DS_Store files
2025-10-22 chore: co-locate datasheets
2025-10-22 chore: co-locate reference design files
2025-10-22 chore: migrate Adafruit reference design to documentation
2025-10-22 chore: remove .DS_Store
2025-10-22 chore: move TI reference designs to documentation
2025-10-22 feat: use symlinks to common project KiCAD footprint library
2025-10-22 feat: include interactive bill of materials for all REV A modulinos
2025-10-22 chore: move Guerrilla RF reference designs to documentation
2025-10-22 chore: replot system testbed schematic describing all modulinos #55
2025-10-22 feat: begin all modulino board directories
2025-10-22 feat: separate RF subsystems for testing using SMA edge launches in testbed KiCAD project #65 #34 #45
2025-10-22 feat: begin USB-PD modulino hardware directory
2025-10-22 docs: begin describing reference design use and "schematic recapture" process #57 #48
2025-10-24 fix: clarify naming of sck pin configuration #82
2025-10-28 feat: begin demo selection code #12 #41
2025-10-28 feat: add config registers and begin single access plus command strobes #45 #81 #82
2025-10-29 chore: added MCU modulino Rev A PCB files to testbed
2025-10-29 feat: include Adafruit PC8575 library and begin port expander #82 #83
2025-10-29 Update Pin Mapping Table.md
    fix: changed reassigned pin numbers
2025-10-31 chore: added additional Rev A PCB file to MCU modulino
2025-11-01 chore: keep BusIO dependency
2025-11-01 feat: create skyworks switch driver #45 #82
2025-11-01 feat: Rotary Encoder Interfacing with HMI Menue #86
2025-11-03 chore: moved Adafruit display sample code from main #86
2025-11-03 feat: refine switch demo and begin amplifier demo #45 #82
2025-11-03 docs: include amplifier startup sequencing #45 #82
2025-11-03 feat: reflect new libraries and begin moving demos #41
2025-11-04 feat: allow passing in PCF port expander instance #83 fix: remove misinterpreted PORT address map
2025-11-04 feat: assign control signals to RF port expander #82
2025-11-04 chore: test code for WROVER - i2c, spi, cores, gpios MCU Testing #83
2025-11-06 Audio PCB Modulino
2025-11-07 feat: move I2C scan debugging into port expander initialization
2025-11-14 Revert "Merge MCU branch with main"
2025-11-15 feat: get SPI transactions working for register access #81
2025-11-15 fix: migrate display updates away from switching logic #82
2025-11-15 chore: move init verification to prep for real transceiver demo #81 #82
2025-11-15 feat: establish display init and config chore: rename folder to display driver chip name
2025-11-16 feat: rewrite most demos for one-time device inits #82
2025-11-17 feat: Added PD Advertisement code PSU PCB Testing Fixes #38
2025-11-19 feat: improve debug printing and include more fonts #86
2025-11-19 feat: better integrate I2C scanner, improve debug printing, allow for storing name of expander #83 #86 #82
2025-11-19 feat: refactor device initialization routines for clarity, remove unused display demo code #86 feat: improve debug printing format and content for demo selection #12 #55
2025-11-19 feat: improve switch demo visuals and debug printing #82
2025-11-19 feat: improve debug printing, relocate interface setup routine #82
2025-11-24 chore: enhance debugging and comments
2025-11-24 fix: simplify access logic feat: begin cc1200 settings
2025-11-24 feat: add hmi and mcu modulinos
2025-11-27 feat: implement frequency deviation and symbol rate register value calculations #82 chore: update build flags to use C++20 language features
2025-11-27 fix: properly clear register fields #82
2025-11-27 feat: begin I2S device drivers
2025-12-01 HMI Firmware Adds to #86 feat: hmi/ui code for display and state update
2025-12-01 MCU Testing & Firmware #83 feat: task structure code and state update
2025-12-01 docs: MCU progress update and todos
2025-12-01 MCU Testing & Firmware Fixes #83 chore: test code for mcu
2025-12-01 fix: update main.cpp in MCU folder, kept separate from the firmware folder to avoid adding in errors before testing the code
2025-12-01 Feat: HMI Code HMI Firmware Fixes #86
2025-12-01 Rename HMI-code to HMI-code.cpp
    added .cpp to make it a C++ file
2025-12-01 Feat: Fuel gauge code (with comments)
2025-12-01 fix: modified function calls
2025-12-01 chore: ignore tests
2025-12-02 feat: improve driver interfacing, continue frequency programming #82
2025-12-02 chore: specify function declarations #82
2025-12-04 feat: mcu demo code and header files, still a work in progress MCU Testing & Firmware #83
2025-12-04 docs: updated Roadmap
2025-12-05 chore: organizes all files on mcu branch
2025-12-06 Audio Reference
2025-12-06 docs: organized REV A and REV B pcb and schematic files and put them into their relavent folders
2025-12-06 docs: added power modulino schematics for Rev A and Rev B
2025-12-06 docs: include device and connector datasheets
2025-12-06 fix: use C string over std::string in printf
2025-12-06 fix: correct RF expander and I2S0 pin assigment, set display rotation
2025-12-06 feat: refine cc1200 driver interface, begin I2S helpers #45
2025-12-06 chore: update VSCode workspace settings
2025-12-06 docs: update README
2025-12-06 docs: update all system schematics for project uniformity
2025-12-07 fix: provide return for playback #91
2025-12-07 feat: write manual calibration routine #82
2025-12-09 docs: addtl CC1200 active mode application note
2025-12-09 feat: begin RSSI freeRTOS timer and task, begin MainTask switch
2025-12-09 fix: change 3D model paths to be in project footprint library
2025-12-10 code: testing knob
2025-12-10 docs: added config code for knob test
2025-12-10 moved demo code
2025-12-12 feat: add BMS and Fuel Gauge libraries and usage
2025-12-12 feat: begin RSSI FreeRTOS Task structure
2025-12-12 feat: add keypad, begin rotary
2025-12-12 feat: taskify switch demo
2025-12-12 fix: begin use of fallback display demo
2025-12-21 fix: make bms task loop
2025-12-21 fix: make adafruit demo rtos friendlier
2025-12-21 chore: complete drawPowerdown tft update isolation
2025-12-21 fix: ensure initializers are blocking
2025-12-21 Revert "Revert "docs: organized REV A and REV B pcb and schematic files and put them into their relavent folders""
2026-02-16 fix: make adafruit display demo rtos friendlier
2026-02-16 feat: utilize fuel gauge and bms libraries
2026-02-16 feat: keypad and scanner routines
2026-02-16 fix: routine-ify using empty loop
2026-02-16 fix: refactor RSSI routine, correct port expander use
